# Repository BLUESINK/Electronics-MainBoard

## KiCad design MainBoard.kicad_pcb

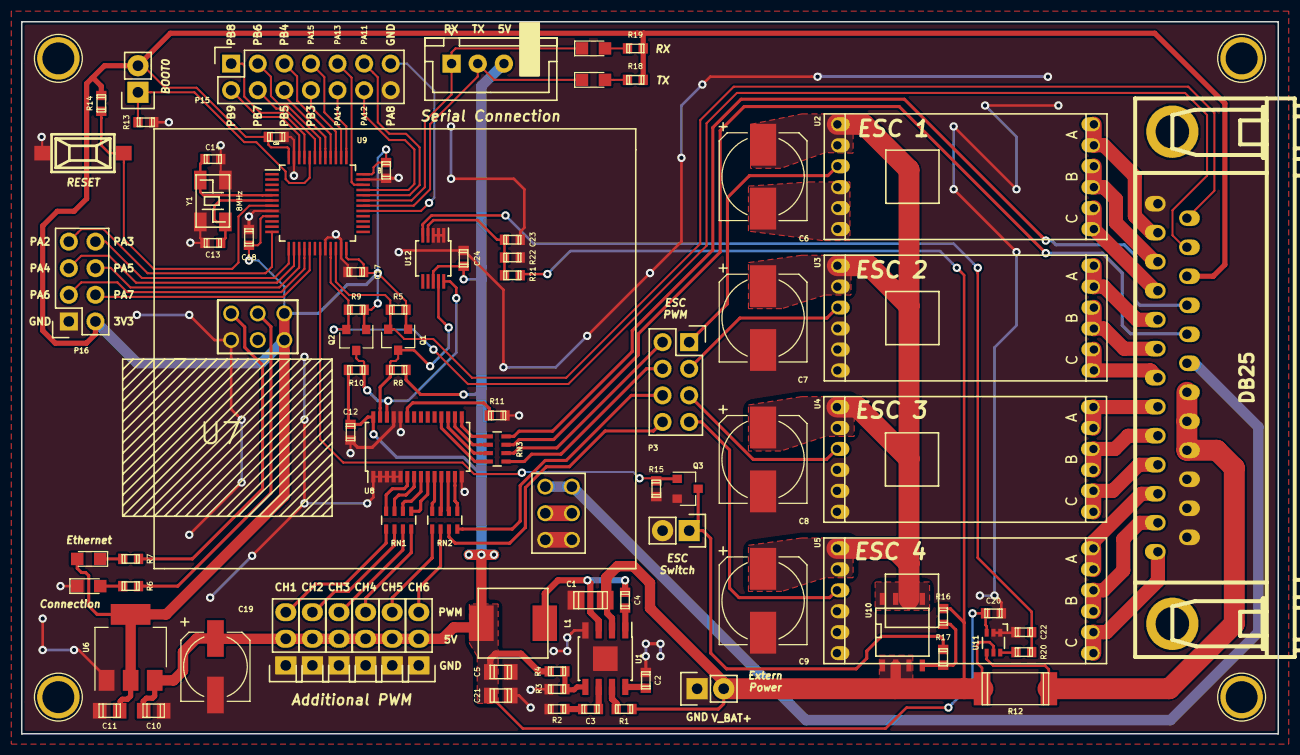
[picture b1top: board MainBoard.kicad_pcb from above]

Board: 2 copper layers, 120.0 x 68.0 mm, 89 parts (0 on the bottom side), 96 nets.

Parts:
C1: 10uF/25V; c_1206
C2, C20, C23, C24: 0.1uF; c_0603
C3: 3.9nF; c_0603
C4: 10nF; c_0603
C5, C21: 22uF/10V; c_0805
C6, C7, C8, C9: 220uF/25V; CP_Elec_8x10
C10, C11: 1uF; c_0805
C12: 10uF; c_0603
C13, C14: 33pF; c_0603
C15, C16, C17, C18, C22: 1uF; c_0603
C19: 220uF/10V; CP_Elec_6.3x5.8
D1, D2, D3, D4: LED; LED_0805
J1: DB25; DB_25M
L1: 10uH/4A; ASPI-0630LR
P1: BOOT; Socket_Strip_Straight_1x02
P2: CONN_01X04; JST_XH_B04B-XH-A_04x2.50mm_Straight
P3, P16: CONN_02X04; Socket_Strip_Straight_2x04
P4, P5, P6, P7: HOLE; 1pin
P8, P14: CONN_01X02; Socket_Strip_Straight_1x02
P9, P10, P11, P12, P13, P18: CONN_01X03; Socket_Strip_Straight_1x03
P15: CONN_02X07; Socket_Strip_Straight_2x07
Q1, Q2: BSS138; SOT-23
Q3: DMN65D8L; SOT-23
R1: 100k; r_0603
R2: 6.8k; r_0603
R3, R22: 10k %1; r_0603
R4: 44.2k 1%; r_0603
R5, R8, R9, R10, R11, R13, R14, R15, R16: 10k; r_0603
R6, R7, R18, R19: 330; r_0603
R12: 0.003 %1; r_2512
R17: 1k; r_0603
R20: 3.3k; r_0603
R21: 30.1k 1%; r_0603
RN1, RN2, RN3: 20k; R_Array_Concave_4x0603
SW1: RESET; smd_push
U1: mp2307; SOIC-8-1EP_3.9x4.9mm_Pitch1.27mm
U2, U3, U4, U5: DYS_mini_ESC; DYS_Mini_ESC
U6: TLV1117LV33; SOT-223
U7: TENDA_P200; Tenda_p200
U8: pca9685; TSSOP-28_4.4x9.7mm_Pitch0.65mm
U9: STM32F103CBT6; LQFP-48_7x7mm_Pitch0.5mm
U10: SI4425DDY; SOIC-8-N
U11: INA199A2; SC-70-6
U12: ADS1015; MSOP-10_3x3mm_Pitch0.5mm
Y1: 8MHz; crystal_maple

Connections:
/3V3: C11.1, C15.1, C16.1, C17.1, C18.1, D2.2, J1.23, P1.2, P16.2, Q1.1, Q2.1, R5.1, R9.1, R14.1, R18.1, R19.1, U6.2, U6.4, U7.3V3, U9.9, U9.24, U9.36, U9.48
/5V: C5.1, C10.1, C12.1, C19.1, C20.1, C21.1, C24.1, L1.2, P2.3, P9.2, P10.2, P11.2, P12.2, P13.2, P18.2, R4.1, R8.1, R10.1, U6.3, U8.28, U11.3, U12.8
/ADC_I: C22.1, R20.1, U12.5
/ADC_V: C23.1, R21.2, R22.1, U12.4
/CH0: P9.3, RN1.1
/CH1: P10.3, RN1.2
/CH2: P11.3, RN1.3
/CH3: P12.3, RN1.4
/CH4: P13.3, RN2.1
/CH5: P18.3, RN2.2
/CH6: P3.8, RN2.3
/CH7: P3.6, RN2.4
/CH10: P3.2, RN3.6
/CH11: P3.4, RN3.5
/ESC1: P3.1, U2.2
/ESC2: P3.3, U3.2
/ESC3: P3.5, U4.2
/ESC4: P3.7, U5.2
/LED1: J1.21, RN3.7
/LED2: J1.22, RN3.8
/MOTOR_1A: J1.12, U2.4
/MOTOR_1B: J1.11, U2.5
/MOTOR_1C: J1.10, U2.6
/MOTOR_2A: J1.9, U3.4
/MOTOR_2B: J1.8, U3.5
/MOTOR_2C: J1.7, U3.6
/MOTOR_3A: J1.6, U4.4
/MOTOR_3B: J1.5, U4.5
/MOTOR_3C: J1.4, U4.6
/MOTOR_4A: J1.3, U5.4
/MOTOR_4B: J1.2, U5.5
/MOTOR_4C: J1.1, U5.6
/OSC_N: C14.1, U9.5, Y1.2
/OSC_P: C13.1, U9.6, Y1.1
/PA2: P16.7, U9.12
/PA3: P16.8, U9.13
/PA4: P16.5, U9.14
/PA5: P16.6, U9.15
/PA6: P16.3, U9.16
/PA7: P16.4, U9.17
/PA8: P15.13, U9.29
/PA11: P15.11, U9.32
/PA12: P15.12, U9.33
/PA13: P15.9, U9.34
/PA14: P15.10, U9.37
/PA15: P15.7, U9.38
/PB3: P15.8, U9.39
/PB4: P15.5, U9.40
/PB5: P15.6, U9.41
/PB6: P15.3, U9.42
/PB7: P15.4, U9.43
/PB8: P15.1, U9.45
/PB9: P15.2, U9.46
/PWR_SW: Q3.1, R15.1, U9.19
/RX1: D4.1, P2.1, U9.31
/SCL_3V3: J1.24, Q2.2, R9.2, U9.21
/SCL_5V: Q2.3, R10.2, U8.26, U12.10
/SDA_3V3: J1.25, Q1.2, R5.2, U9.22
/SDA_5V: Q1.3, R8.2, U8.27, U12.9
/T+: J1.20, U7.T_+
/TX1: D3.1, P2.2, U9.30
/V_BAT: C1.1, P8.2, R1.1, R12.1, R16.1, R21.1, U1.2, U10.1, U10.2, U10.3, U11.5
/V_IN: J1.17, J1.18, J1.19, R12.2, U11.4
/V_PWR: C6.1, C7.1, C8.1, C9.1, U2.3, U3.3, U4.3, U5.3, U10.5, U10.6, U10.7, U10.8
GND: C1.2, C2.2, C5.2, C6.2, C7.2, C8.2, C9.2, C10.2, C11.2, C12.2, C13.2, C14.2, C15.2, C16.2, C17.2, C18.2, C19.2, C20.2, C21.2, C22.2, C23.2, C24.2, D1.1, J1.13, J1.14, J1.15, J1.16, P2.4, P8.1, P9.1, P10.1, P11.1, P12.1, P13.1, P14.2, P15.14, P16.1, P18.1, Q3.2, R2.2, R3.2, R11.2, R13.1, R15.2, R22.2, SW1.1, U1.4, U1.9, U2.1, U3.1, U4.1, U5.1, U6.1, U7.GND, U7.T_-, U8.1, U8.2, U8.3, U8.4, U8.5, U8.14, U8.24, U8.25, U9.8, U9.20, U9.23, U9.35, U9.47, U11.1, U11.2, U12.1, U12.2, U12.3, Y1.3
unnamed: C2.1, U1.8
unnamed: C3.1, U1.6
unnamed: C3.2, R2.1
unnamed: C4.1, L1.1, U1.3
unnamed: C4.2, U1.1
unnamed: D1.2, R6.2
unnamed: D2.1, R7.2
unnamed: D3.2, R18.2
unnamed: D4.2, R19.2
unnamed: P1.1, R13.2, U9.44
unnamed: P14.1, Q3.3, R17.2
unnamed: R1.2, U1.7
unnamed: R3.1, R4.2, U1.5
unnamed: R6.1, U7.C
unnamed: R7.1, U7.E
unnamed: R11.1, U8.23
unnamed: R14.2, SW1.2, U9.7
unnamed: R16.2, R17.1, U10.4
unnamed: R20.2, U11.6
unnamed: RN1.5, U8.9
unnamed: RN1.6, U8.8
unnamed: RN1.7, U8.7
unnamed: RN1.8, U8.6
unnamed: RN2.5, U8.13
unnamed: RN2.6, U8.12
unnamed: RN2.7, U8.11
unnamed: RN2.8, U8.10
unnamed: RN3.1, U8.15
unnamed: RN3.2, U8.16
unnamed: RN3.3, U8.17
unnamed: RN3.4, U8.18

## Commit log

2017-01-05 add lib file
2017-01-05 main board update
2017-01-07 First layout finish
2017-01-10 Make schematic
2017-01-10 Add BOM
2017-01-10 Update schematic
2017-01-11 Change db25 footprint
2017-01-13 pull up rx/tx indicate led & change esc capacitor size
2017-01-16 change plc module position
2017-01-17 change regulator position
2017-01-18 v.0.1
2017-01-18 routing...
2017-01-19 move pwm pin position
2017-01-20 Add current & voltage sensor
2017-01-22 replace groud via
2017-01-22 Update BOM
2017-01-24 Fix pcb-silk
2017-01-26 Fix ina199a2 routing
